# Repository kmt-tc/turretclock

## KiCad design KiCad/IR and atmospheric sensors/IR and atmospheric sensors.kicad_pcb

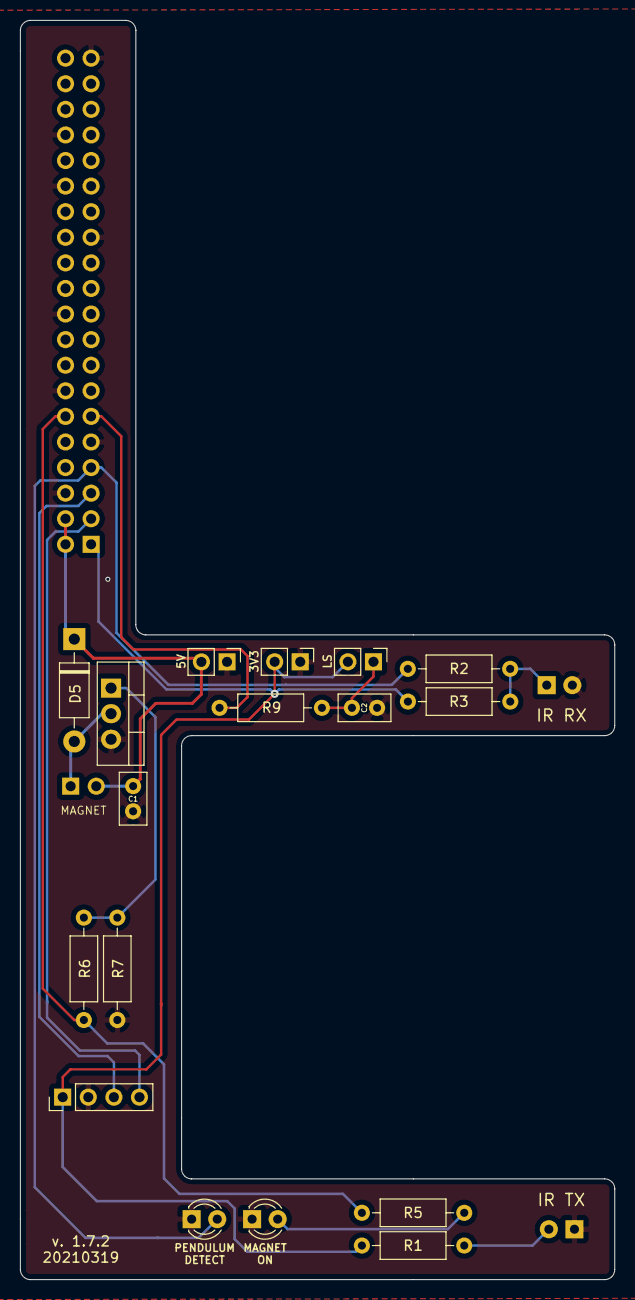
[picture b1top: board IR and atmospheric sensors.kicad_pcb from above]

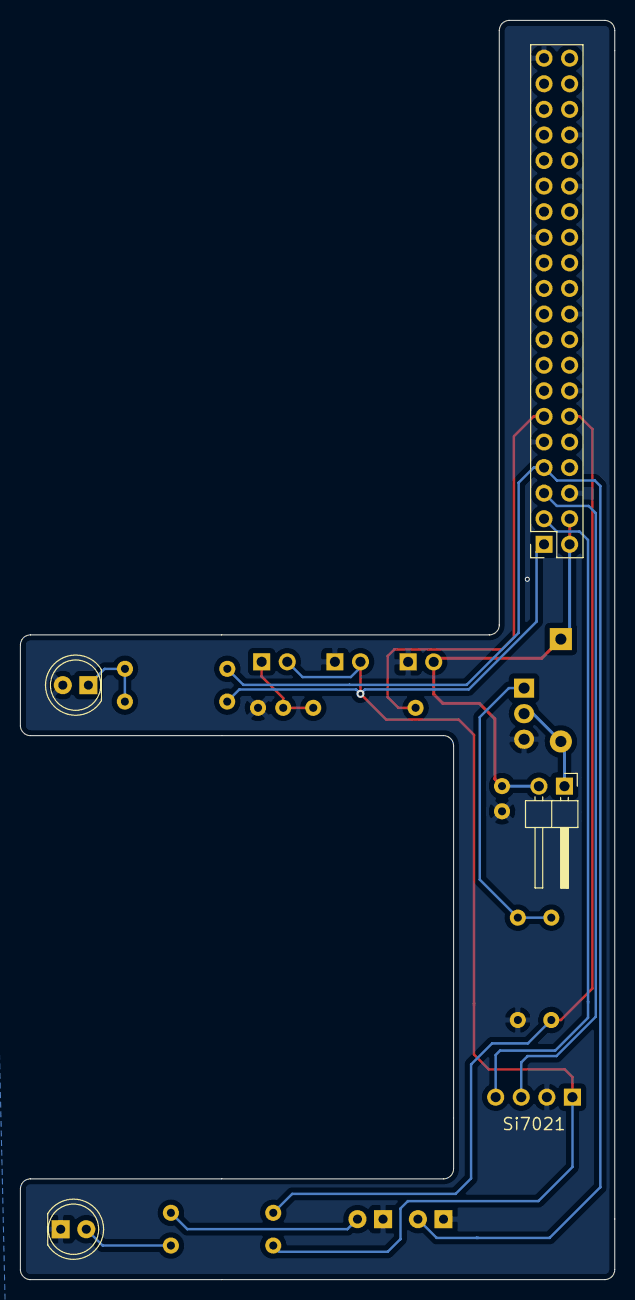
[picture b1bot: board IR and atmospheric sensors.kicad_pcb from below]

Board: 2 copper layers, 59.0 x 125.0 mm, 21 parts (4 on the bottom side), 14 nets.

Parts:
C1: 0.1; C_Disc_D5.0mm_W2.5mm_P2.50mm
C2: 1; C_Disc_D5.0mm_W2.5mm_P2.50mm
D1: IR LED; LED_D5.0mm_IRGrey
D2: IR RX; LED_D5.0mm_IRGrey
D3, D4: LED; LED_D3.0mm
D5: 1N5817; D_DO-41_SOD81_P10.16mm_Horizontal
J1: Raspberry Pi; PinSocket_2x20_P2.54mm_Vertical
J2, J3: Conn_01x02_Male; PinHeader_1x02_P2.54mm_Vertical
L1: Electromagnetic_Actor; PinHeader_1x02_P2.54mm_Horizontal
Q1: IRLZ34N; TO-220-3_Vertical
R1, R2: 470; R_Axial_DIN0207_L6.3mm_D2.5mm_P10.16mm_Horizontal
R3: 10K; R_Axial_DIN0207_L6.3mm_D2.5mm_P10.16mm_Horizontal
R5: 330; R_Axial_DIN0207_L6.3mm_D2.5mm_P10.16mm_Horizontal
R6, R9: 100; R_Axial_DIN0207_L6.3mm_D2.5mm_P10.16mm_Horizontal
R7: 100K; R_Axial_DIN0207_L6.3mm_D2.5mm_P10.16mm_Horizontal
R8: R_PHOTO; PinHeader_1x02_P2.54mm_Vertical
U1: Si7021; PinHeader_1x04_P2.54mm_Vertical

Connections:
/3V3: J1.1, J1.17, J3.2, R1.1, R3.2, R8.2, U1.1
/5V: C1.1, D5.1, J1.2, J1.4, J2.2, L1.2
/GPIO4: D3.2, J1.7, R2.1
/GPIO17: J1.11, R9.2
/GPIO18: J1.12, R5.1, R6.2
/SCL: J1.5, U1.3
/SDA: J1.3, U1.4
GND: C1.2, C2.2, D1.1, D2.2, D3.1, D4.1, J1.6, J1.9, J1.14, J1.20, J1.25, J1.30, J1.34, J1.39, J2.1, J3.1, Q1.3, R7.2, U1.2
unnamed: C2.1, R8.1, R9.1
unnamed: D1.2, R1.2
unnamed: D2.1, R2.2, R3.1
unnamed: D4.2, R5.2
unnamed: D5.2, L1.1, Q1.2
unnamed: Q1.1, R6.1, R7.1

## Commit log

2021-04-15 2021041502
2021-04-15 2021041601
2021-04-16 reworked averages
2021-04-18 int on avgskew might be causing incorrect drift average computation
2021-04-21 fix permissions on turretclock.py
2021-04-21 reconnect to broker on disconnect
2021-04-22 allow timestamps to be trimmed by 0 characters
2021-04-22 trash cleanup
2021-04-22 timeout command checks/cleanup
2021-05-03 add clock error to database and snmp stats
2021-06-09 don't fail history averaging if there's old data in the database
2021-06-09 empty database telemetry fixes
2021-07-12 Uploaded KiCad document for sensor hardware
2021-07-12 Don't need this file
2021-07-27 reworked temperature, humidity variables to fix CLI execution and removed some old debug code
2021-11-21 reworked hz and drift calculations slightly
2021-11-21 Hz display should be more precise
2021-11-27 incorporate ntpd-computed oscillator drift to fix pendulum timing errors
2021-11-27 added oscillator drift to status line
2021-11-27 reread ntp.drift file only when it changes
2021-11-28 removed unnecessary test in ntp drift file read routine
2021-11-29 simplified 24 hour drift average calculation
2021-11-29 move ntp.drift reader into main module
2021-11-29 add state file saving/loading
2021-11-30 rework drift average reporting to MQTT
2021-11-30 remove unnecessary (and ugly and buggy) database code
2021-11-30 no need to compute drift averages twice
2022-03-30 change p_min to p_maxskew to better reject bad data
2022-03-30 preview commit incomplete
2022-03-31 need to reset the watchdog even after bad reads
2022-04-01 set prevArr even in event of bad beat
